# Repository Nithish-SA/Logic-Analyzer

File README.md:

# Logic-Analyzer
A 16 channel at 100Mhz Logic Analyzer which is supported by Cypress FX3 (USB 3.0 MCU).

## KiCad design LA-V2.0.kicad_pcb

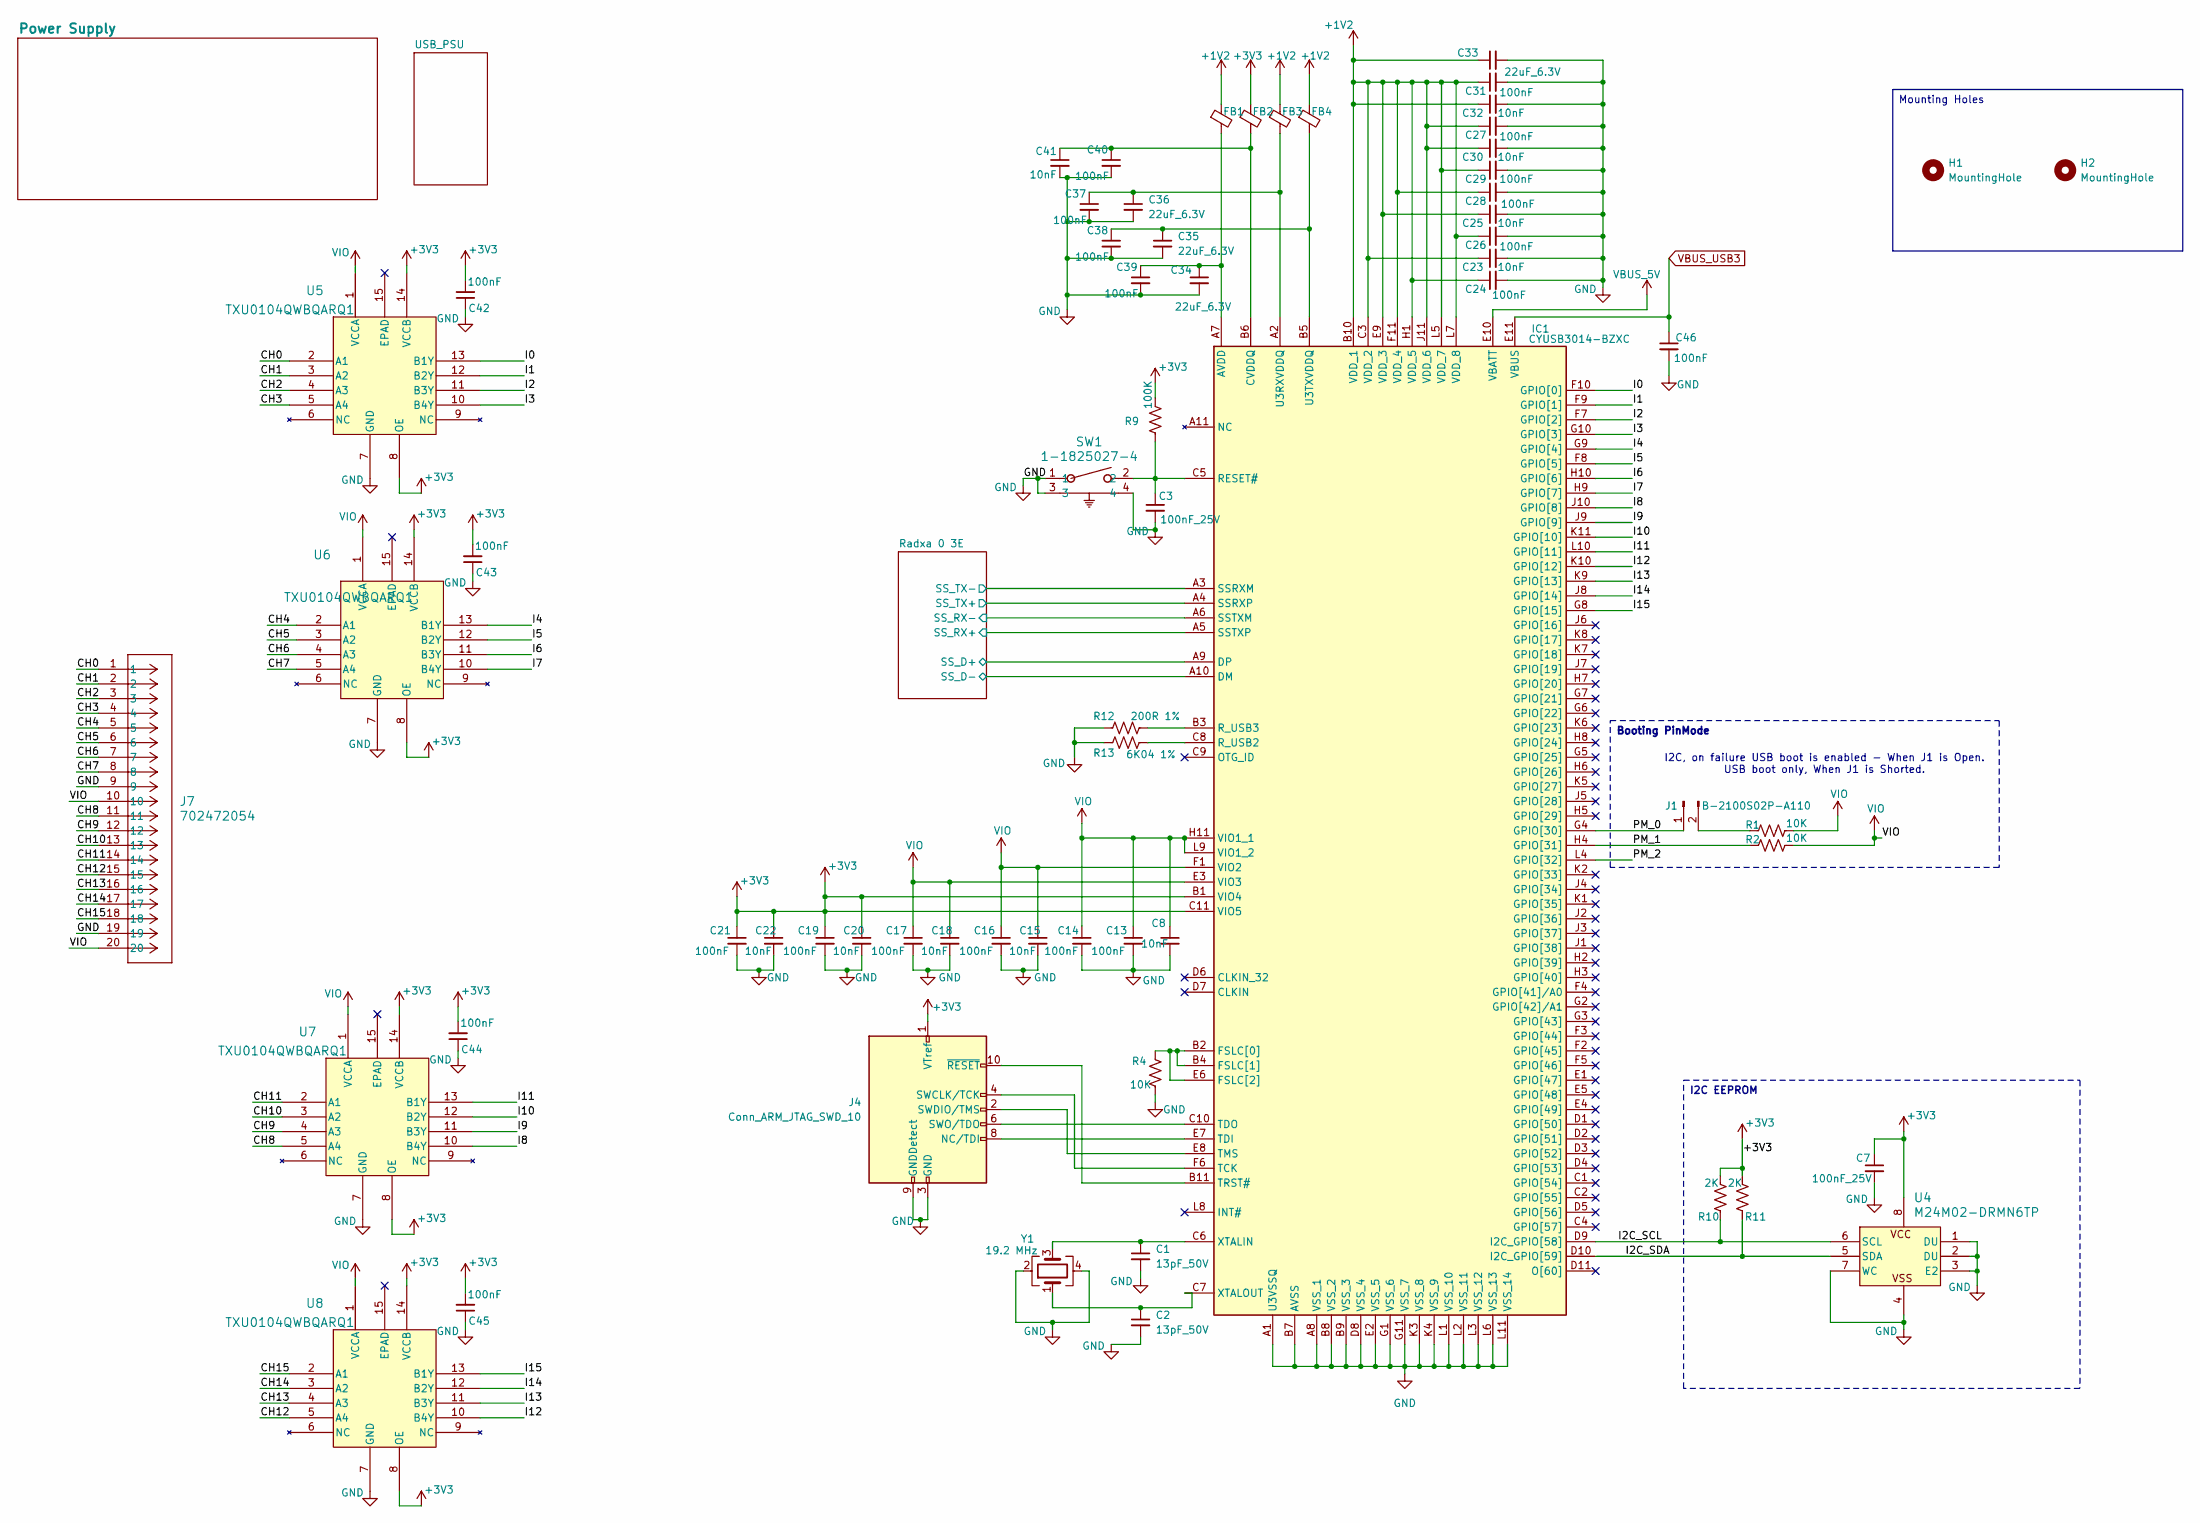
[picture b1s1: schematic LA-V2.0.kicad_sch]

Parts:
C1, C2: 13pF_50V; C_0402_1005Metric; LCSC Part# C161306
C3, C7: 100nF_25V; C_0402_1005Metric; LCSC Part# C155422
C8, C15, C18, C20, C22, C23, C25, C30, C32, C41: 10nF; C_0402_1005Metric; LCSC Part# C60133
C13, C14, C16, C17, C19, C21, C24, C26, C27, C28, C29, C31, C37, C38, C39, C40, C42, C43, C44, C45, C46: 100nF; C_0402_1005Metric; LCSC Part# C155422
C33: 22uF_6.3V; C_0805_2012Metric; LCSC Part# C5674
C34, C35, C36: 22uF_6.3V; C_0402_1005Metric; LCSC Part# C415703
FB1, FB2, FB3, FB4: FerriteBead_Small; L_0805_2012Metric; LCSC Part# C81034
H1, H2: MountingHole; MountingHole_2.7mm_M2.5_ISO14580_Pad_TopOnly
IC1: CYUSB3014-BZXC; Manufacturer_Part_Number CYUSB3014-BZXC; LCSC Part# C462526
J1: B-2100S02P-A110; PinHeader_1x02_P2.54mm_Vertical; LCSC Part# C124375
J4: Conn_ARM_JTAG_SWD_10; PinHeader_2x05_P2.54mm_Vertical; LCSC Part# C492422
J7: 702472054; CONN_7024720xx_MOL; LCSC Part# C17505050
R1, R2, R4: 10K; R_0402_1005Metric; LCSC Part# C60490
R9: 100K; R_0805_2012Metric; LCSC Part# C122537
R10, R11: 2K; R_0805_2012Metric; LCSC Part# C114572
R12: 200R 1%; R_0402_1005Metric; LCSC Part# C114764
R13: 6K04 1%; R_0805_2012Metric; LCSC Part# C3014413
SW1: 1-1825027-4; SW2_1825027-E_TEC; LCSC Part# C2928195
U4: M24M02-DRMN6TP; SO_RMN6TP_STM; LCSC Part# C115042
U5, U6, U7, U8: TXU0104QWBQARQ1; WQFN14_BQA_TEX; LCSC Part# C5217874
Y1: 19.2 MHz; Crystal_SMD_3225-4Pin_3.2x2.5mm; LCSC Part# C7294560

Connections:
+1V2: C23.1, C24.1, C25.1, C26.1, C27.1, C28.1, C29.1, C30.1, C31.1, C32.1, C33.1, FB1.1, FB3.1, FB4.1, IC1.B10 (VDD_1), IC1.C3 (VDD_2), IC1.E9 (VDD_3), IC1.F11 (VDD_4), IC1.H1 (VDD_5), IC1.J11 (VDD_6), IC1.L5 (VDD_7), IC1.L7 (VDD_8); also elsewhere on the board
+3V3: C7.1, C19.1, C20.1, C21.1, C22.1, C42.2, C43.2, C44.2, C45.2, FB2.1, IC1.B1 (VIO4), IC1.C11 (VIO5), J4.1 (VTref), R9.2, R10.2, R11.2, U4.8, U5.8 (OE), U5.14 (VCCB), U6.8 (OE), U6.14 (VCCB), U7.8 (OE), U7.14 (VCCB), U8.8 (OE), U8.14 (VCCB); also elsewhere on the board
/CH0: J7.1, U5.2 (A1)
/CH1: J7.2, U5.3 (A2)
/CH2: J7.3, U5.4 (A3)
/CH3: J7.4, U5.5 (A4)
/CH4: J7.5, U6.2 (A1)
/CH5: J7.6, U6.3 (A2)
/CH6: J7.7, U6.4 (A3)
/CH7: J7.8, U6.5 (A4)
/CH8: J7.11, U7.5 (A4)
/CH9: J7.12, U7.4 (A3)
/CH10: J7.13, U7.3 (A2)
/CH11: J7.14, U7.2 (A1)
/CH12: J7.15, U8.5 (A4)
/CH13: J7.16, U8.4 (A3)
/CH14: J7.17, U8.3 (A2)
/CH15: J7.18, U8.2 (A1)
/I0: IC1.F10 (GPIO[0]), U5.13 (B1Y)
/I1: IC1.F9 (GPIO[1]), U5.12 (B2Y)
/I2: IC1.F7 (GPIO[2]), U5.11 (B3Y)
/I2C_SCL: IC1.D9 (I2C_GPIO[58]), R10.1, U4.6 (SCL)
/I2C_SDA: IC1.D10 (I2C_GPIO[59]), R11.1, U4.5 (SDA)
/I3: IC1.G10 (GPIO[3]), U5.10 (B4Y)
/I4: IC1.G9 (GPIO[4]), U6.13 (B1Y)
/I5: IC1.F8 (GPIO[5]), U6.12 (B2Y)
/I6: IC1.H10 (GPIO[6]), U6.11 (B3Y)
/I7: IC1.H9 (GPIO[7]), U6.10 (B4Y)
/I8: IC1.J10 (GPIO[8]), U7.10 (B4Y)
/I9: IC1.J9 (GPIO[9]), U7.11 (B3Y)
/I10: IC1.K11 (GPIO[10]), U7.12 (B2Y)
/I11: IC1.L10 (GPIO[11]), U7.13 (B1Y)
/I12: IC1.K10 (GPIO[12]), U8.10 (B4Y)
/I13: IC1.K9 (GPIO[13]), U8.11 (B3Y)
/I14: IC1.J8 (GPIO[14]), U8.12 (B2Y)
/I15: IC1.G8 (GPIO[15]), U8.13 (B1Y)
/PM_0: IC1.G4 (GPIO[30]), J1.1
/PM_1: IC1.H4 (GPIO[31]), R2.1
/PM_2: IC1.L4 (GPIO[32])
/Radxa 0 3E/SS_D+: IC1.A9 (DP); also elsewhere on the board
/Radxa 0 3E/SS_D-: IC1.A10 (DM); also elsewhere on the board
/Radxa 0 3E/SS_RX+: IC1.A5 (SSTXP); also elsewhere on the board
/Radxa 0 3E/SS_RX-: IC1.A6 (SSTXM); also elsewhere on the board
/Radxa 0 3E/SS_TX+: IC1.A4 (SSRXP); also elsewhere on the board
/Radxa 0 3E/SS_TX-: IC1.A3 (SSRXM); also elsewhere on the board
GND: C1.2, C2.2, C3.2, C7.2, C8.2, C13.2, C14.2, C15.2, C16.2, C17.2, C18.2, C19.2, C20.2, C21.2, C22.2, C23.2, C24.2, C25.2, C26.2, C27.2, C28.2, C29.2, C30.2, C31.2, C32.2, C33.2, C34.2, C35.2, C36.2, C37.2, C38.2, C39.2, C40.2, C41.2, C42.1, C43.1, C44.1, C45.1, C46.2, IC1.A1 (U3VSSQ), IC1.A8 (VSS_1), IC1.B7 (AVSS), IC1.B8 (VSS_2), IC1.B9 (VSS_3), IC1.D8 (VSS_4), IC1.E2 (VSS_5), IC1.G1 (VSS_6), IC1.G11 (VSS_7), IC1.K3 (VSS_8), IC1.K4 (VSS_9), IC1.L1 (VSS_10), IC1.L2 (VSS_11), IC1.L3 (VSS_12), IC1.L6 (VSS_13), IC1.L11 (VSS_14), J4.3 (GND), J4.5 (GND), J4.9 (GNDDetect), J7.9, J7.19, R4.1, R12.2, R13.2, SW1.1, SW1.3, SW1.4, U4.1 (DU), U4.2 (DU), U4.3 (E2), U4.4, U4.7 (WC), U5.7 (GND), U6.7 (GND), U7.7 (GND), U8.7 (GND), Y1.2, Y1.4; also elsewhere on the board
unnamed: C34.1, C39.1, FB1.2, IC1.A7 (AVDD)
unnamed: C40.1, C41.1, FB2.2, IC1.B6 (CVDDQ)
unnamed: IC1.B2 (FSLC[0]), IC1.B4 (FSLC[1]), IC1.E6 (FSLC[2]), R4.2
unnamed: C3.1, IC1.C5 (RESET#), R9.1, SW1.2
unnamed: IC1.C8 (R_USB2), R13.1
unnamed: IC1.B3 (R_USB3), R12.1
unnamed: IC1.F6 (TCK), J4.4 (SWCLK/TCK)
unnamed: IC1.E7 (TDI), J4.8 (NC/TDI)
unnamed: IC1.C10 (TDO), J4.6 (SWO/TDO)
unnamed: IC1.E8 (TMS), J4.2 (SWDIO/TMS)
unnamed: IC1.B11 (TRST#), J4.10 (~RESET)
unnamed: C36.1, C37.1, FB3.2, IC1.A2 (U3RXVDDQ)
unnamed: C35.1, C38.1, FB4.2, IC1.B5 (U3TXVDDQ)
unnamed: C1.1, IC1.C6 (XTALIN), Y1.3
unnamed: C2.1, IC1.C7 (XTALOUT), Y1.1
unnamed: J1.2, R1.1
VBUS_5V: IC1.E10 (VBATT); also elsewhere on the board
VBUS_USB3: C46.1, IC1.E11 (VBUS); also elsewhere on the board
VIO: C8.1, C13.1, C14.1, C15.1, C16.1, C17.1, C18.1, IC1.E3 (VIO3), IC1.F1 (VIO2), IC1.H11 (VIO1_1), IC1.L9 (VIO1_2), J7.10, J7.20, R1.2, R2.2, U5.1 (VCCA), U6.1 (VCCA), U7.1 (VCCA), U8.1 (VCCA); also elsewhere on the board

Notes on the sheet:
I2C, on failure USB boot is enabled - When J1 is Open. USB boot only, When J1 is Shorted.
Booting PinMode
I2C EEPROM
Mounting Holes

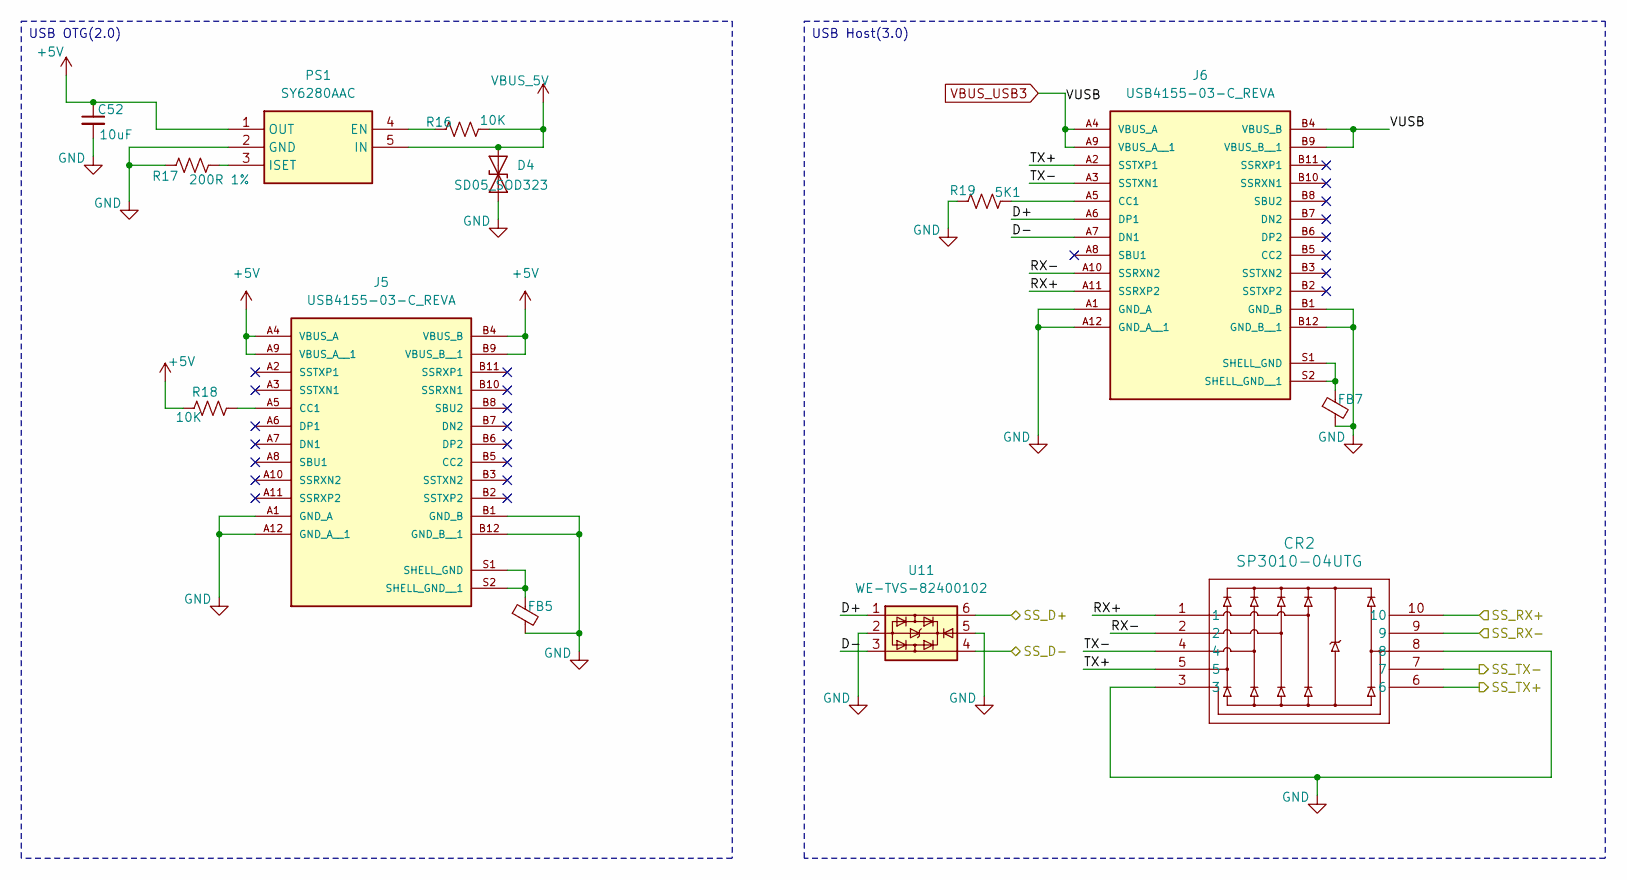
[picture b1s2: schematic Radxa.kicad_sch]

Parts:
C52: 10uF; C_0402_1005Metric; LCSC Part# C32635
CR2: SP3010-04UTG; UDFEN-10_MO229_LTF-L; LCSC Part# C126837
D4: SD05_SOD323; D_SOD-323
FB5, FB7: FerriteBead_Small; L_0805_2012Metric; LCSC Part# C81034
J5, J6: USB4155-03-C_REVA; USB Plug-GCT_USB4155-03-C_REVA; PARTREV A
PS1: SY6280AAC; SOT95P285X140-5N; Manufacturer_Part_Number SY6280AAC
R16, R18: 10K; R_0402_1005Metric; LCSC Part# C60490
R17: 200R 1%; R_0402_1005Metric; LCSC Part# C114764
R19: 5K1; R_0402_1005Metric; LCSC Part# C351692
U11: WE-TVS-82400102; SOT-23-6; LCSC Part# C22435120

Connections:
+5V: C52.1, J5.A4 (VBUS_A), J5.A9 (VBUS_A__1), J5.B4 (VBUS_B), J5.B9 (VBUS_B__1), PS1.1 (OUT), R18.1
/Radxa 0 3E/D+: J6.A6 (DP1), U11.1
/Radxa 0 3E/D-: J6.A7 (DN1), U11.3
/Radxa 0 3E/RX+: CR2.1, J6.A11 (SSRXP2)
/Radxa 0 3E/RX-: CR2.2, J6.A10 (SSRXN2)
/Radxa 0 3E/SS_D+: U11.6; also elsewhere on the board
/Radxa 0 3E/SS_D-: U11.4; also elsewhere on the board
/Radxa 0 3E/SS_RX+: CR2.10; also elsewhere on the board
/Radxa 0 3E/SS_RX-: CR2.9; also elsewhere on the board
/Radxa 0 3E/SS_TX+: CR2.6; also elsewhere on the board
/Radxa 0 3E/SS_TX-: CR2.7; also elsewhere on the board
/Radxa 0 3E/TX+: CR2.5, J6.A2 (SSTXP1)
/Radxa 0 3E/TX-: CR2.4, J6.A3 (SSTXN1)
GND: C52.2, CR2.3, CR2.8, D4.1 (A1), FB5.2, FB7.2, J5.A1 (GND_A), J5.A12 (GND_A__1), J5.B1 (GND_B), J5.B12 (GND_B__1), J6.A1 (GND_A), J6.A12 (GND_A__1), J6.B1 (GND_B), J6.B12 (GND_B__1), PS1.2 (GND), R17.2, R19.2, U11.2, U11.5; also elsewhere on the board
unnamed: J5.A5 (CC1), R18.2
unnamed: FB5.1, J5.S1 (SHELL_GND), J5.S2 (SHELL_GND__1)
unnamed: J6.A5 (CC1), R19.1
unnamed: FB7.1, J6.S1 (SHELL_GND), J6.S2 (SHELL_GND__1)
unnamed: PS1.4 (EN), R16.1
unnamed: PS1.3 (ISET), R17.1
VBUS_5V: D4.2 (A2), PS1.5 (IN), R16.2; also elsewhere on the board
VBUS_USB3: J6.A4 (VBUS_A), J6.A9 (VBUS_A__1), J6.B4 (VBUS_B), J6.B9 (VBUS_B__1); also elsewhere on the board

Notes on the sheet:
USB OTG(2.0)
USB Host(3.0)

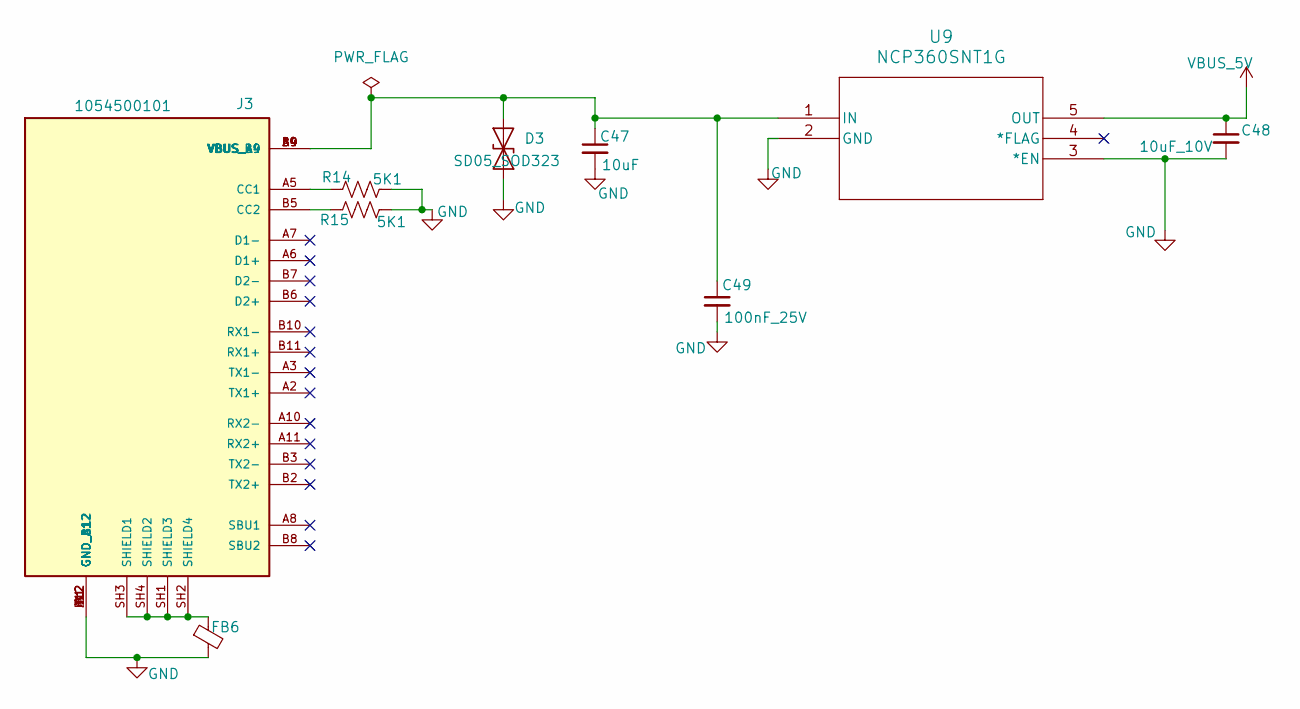
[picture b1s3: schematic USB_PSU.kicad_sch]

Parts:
C47: 10uF; C_0402_1005Metric; LCSC Part# C32635
C48: 10uF_10V; C_0402_1005Metric; LCSC Part# C32635
C49: 100nF_25V; C_0402_1005Metric; LCSC Part# C155422
D3: SD05_SOD323; D_SOD-323
FB6: FerriteBead_Small; L_0805_2012Metric; LCSC Part# C81034
J3: 1054500101; MOLEX_1054500101; PARTREV A7; LCSC Part# C134092
R14, R15: 5K1; R_0402_1005Metric; LCSC Part# C351692
U9: NCP360SNT1G; TSOP5_3X1P5_ONS; LCSC Part# C603707

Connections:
GND: C47.2, C48.2, C49.2, D3.1 (A1), FB6.2, J3.A1 (GND_A1), J3.A12 (GND_A12), J3.B1 (GND_B1), J3.B12 (GND_B12), R14.1, R15.1, U9.2 (GND), U9.3 (*EN); also elsewhere on the board
unnamed: C47.1, C49.1, D3.2 (A2), J3.A4 (VBUS_A4), J3.A9 (VBUS_A9), J3.B4 (VBUS_B4), J3.B9 (VBUS_B9), U9.1 (IN)
unnamed: J3.A5 (CC1), R14.2
unnamed: J3.B5 (CC2), R15.2
unnamed: FB6.1, J3.SH1 (SHIELD3), J3.SH2 (SHIELD4), J3.SH3 (SHIELD1), J3.SH4 (SHIELD2)
VBUS_5V: C48.1, U9.5 (OUT); also elsewhere on the board

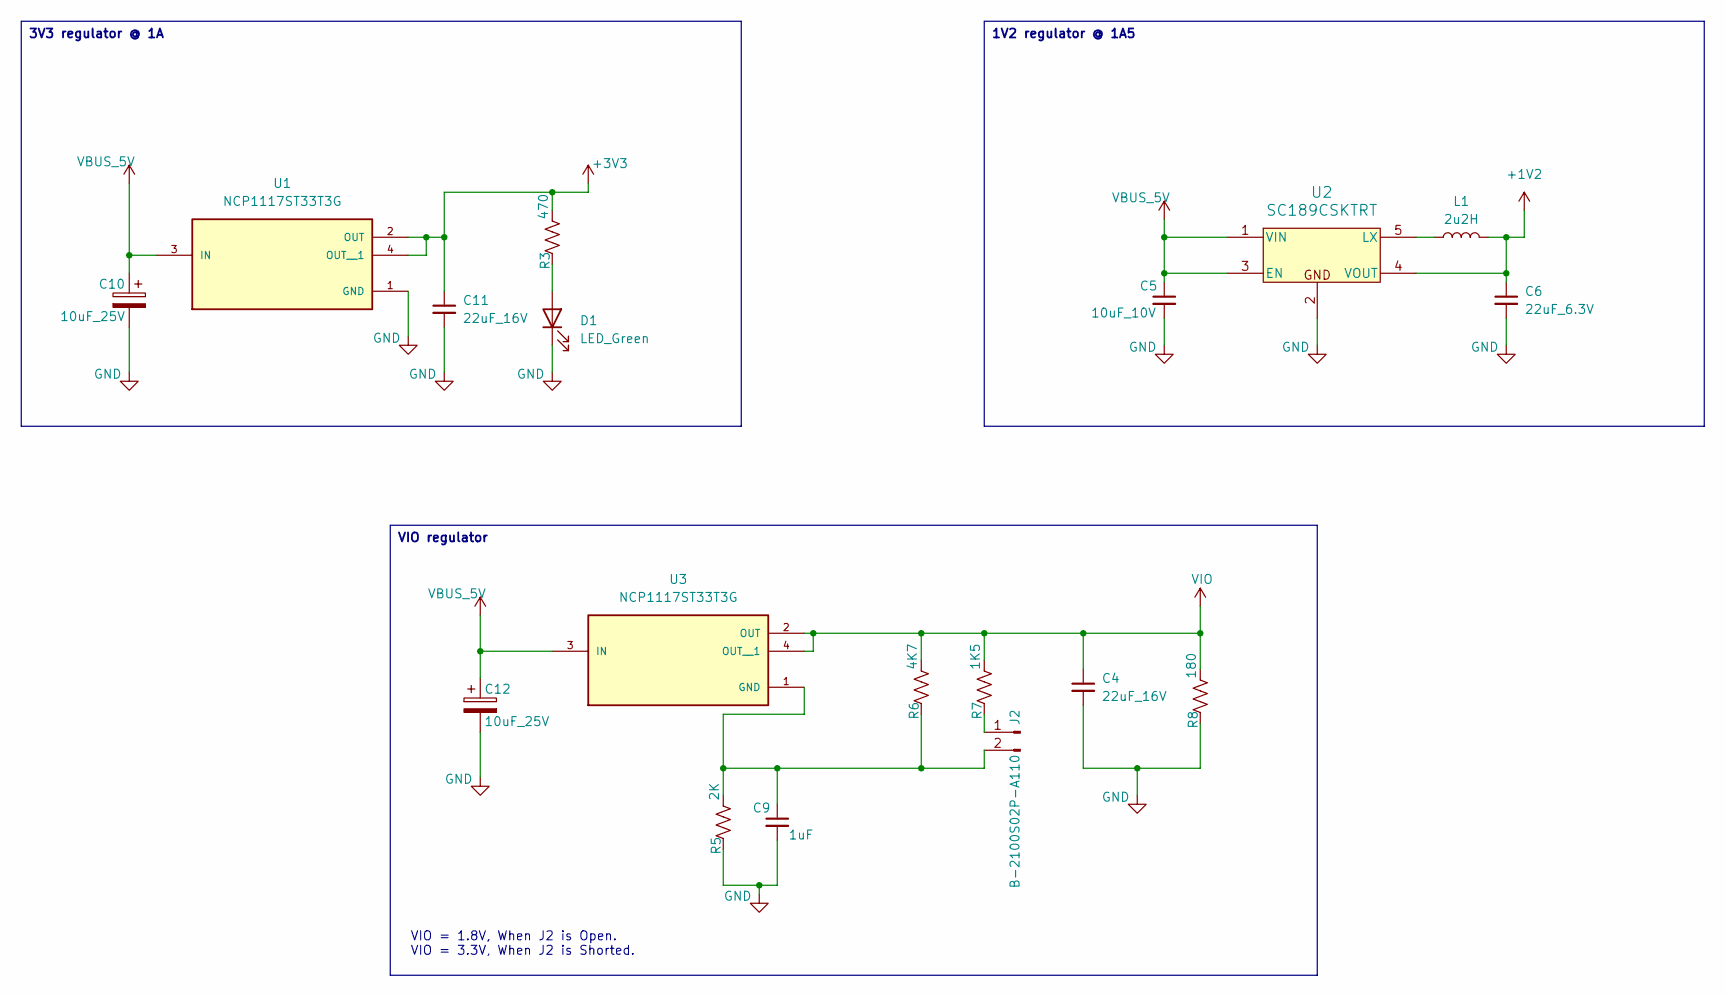
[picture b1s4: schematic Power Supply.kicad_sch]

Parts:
C4, C11: 22uF_16V; C_0805_2012Metric; LCSC Part# C296720
C5: 10uF_10V; C_0805_2012Metric; LCSC Part# C32635
C6: 22uF_6.3V; C_0805_2012Metric; LCSC Part# C5674
C9: 1uF; C_0603_1608Metric; Mfg PN CL10A105KP8NNNC; LCSC Part# C26413
C10, C12: 10uF_25V; CP_EIA-3528-12_Kemet-T; LCSC Part# C382102
D1: LED_Green; LED_0805_2012Metric; LCSC Part# C98221
J2: B-2100S02P-A110; PinHeader_1x02_P2.54mm_Vertical; LCSC Part# C124375
L1: 2u2H; L_0805_2012Metric; LCSC Part# C711165
R3: 470; R_0603_1608Metric; LCSC Part# C881392
R5: 2K; R_0805_2012Metric; LCSC Part# C114572
R6: 4K7; R_0805_2012Metric; LCSC Part# C60816
R7: 1K5; R_0805_2012Metric; LCSC Part# C865270
R8: 180; R_0805_2012Metric; LCSC Part# C137585
U1, U3: NCP1117ST33T3G; SOT230P700X180-4N
U2: SC189CSKTRT; SOT_CSKTRT_SEM; LCSC Part# C783594

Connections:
+1V2: C6.1, L1.2, U2.4 (VOUT); also elsewhere on the board
+3V3: C11.1, R3.2, U1.2 (OUT), U1.4 (OUT__1); also elsewhere on the board
GND: C4.2, C5.2, C6.2, C9.2, C10.2, C11.2, C12.2, D1.1 (K), R5.1, R8.1, U1.1 (GND), U2.2; also elsewhere on the board
unnamed: D1.2 (A), R3.1
unnamed: J2.1, R7.1
unnamed: C9.1, J2.2, R5.2, R6.1, U3.1 (GND)
unnamed: L1.1, U2.5 (LX)
VBUS_5V: C5.1, C10.1, C12.1, U1.3 (IN), U2.1 (VIN), U2.3 (EN), U3.3 (IN); also elsewhere on the board
VIO: C4.1, R6.2, R7.2, R8.2, U3.2 (OUT), U3.4 (OUT__1); also elsewhere on the board

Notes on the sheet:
VIO = 1.8V, When J2 is Open. VIO = 3.3V, When J2 is Shorted.
3V3 regulator @ 1A
VIO regulator
1V2 regulator @ 1A5

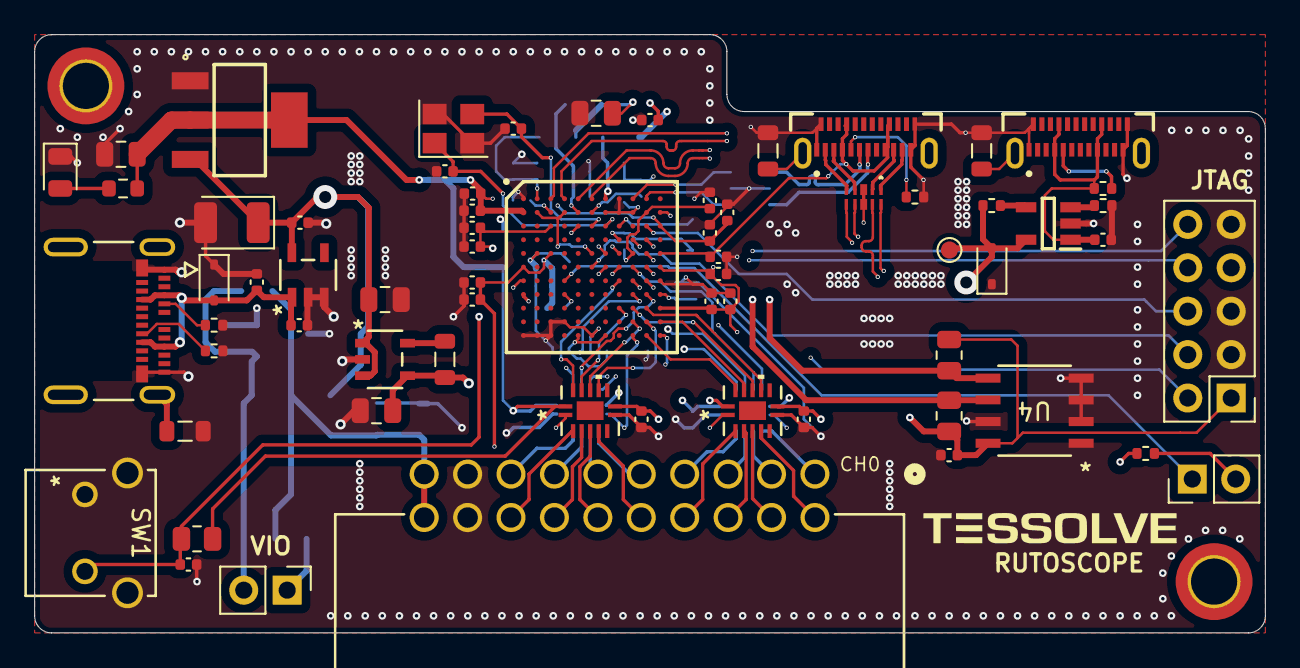
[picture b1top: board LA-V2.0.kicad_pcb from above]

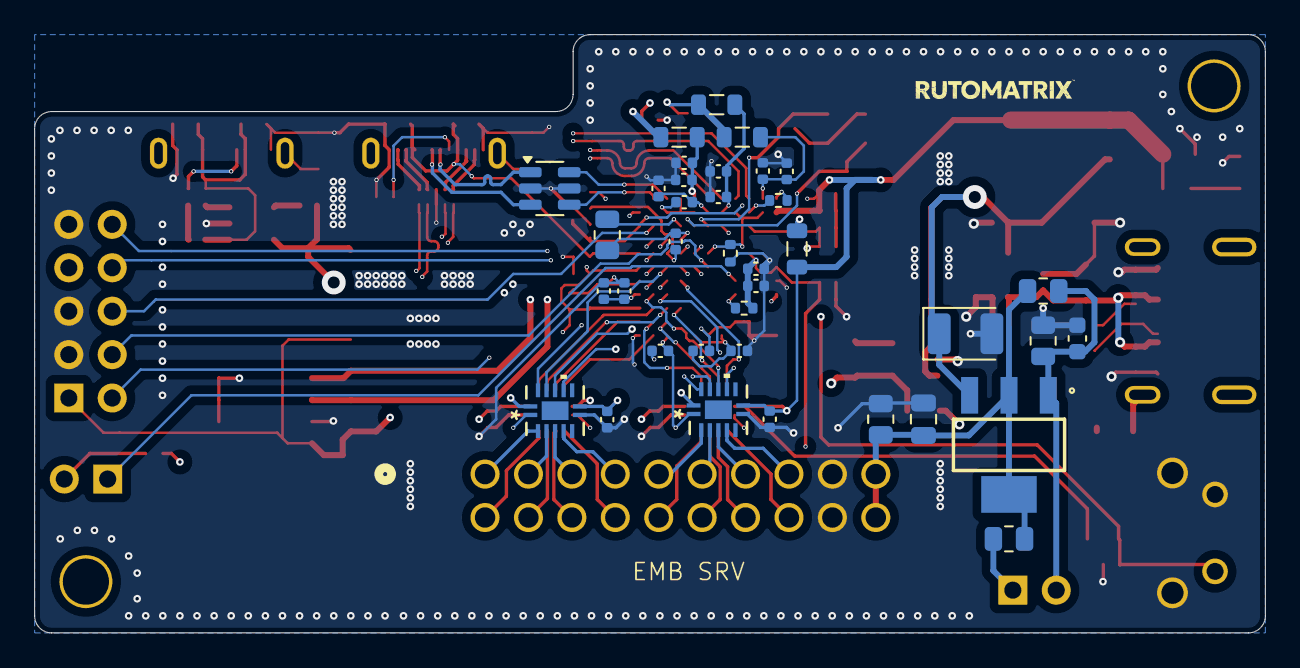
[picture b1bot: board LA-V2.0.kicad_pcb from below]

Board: 4 copper layers, 72.0 x 35.0 mm, 105 parts (37 on the bottom side), 85 nets.

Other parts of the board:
TP1: TestPoint_Pad_D1.0mm

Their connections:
VBUS_5V: TP1.1; also elsewhere on the board

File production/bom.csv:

Designator,Footprint,Quantity,Value,LCSC Part #
"C1, C2",0402,2,13pF_50V,
"C10, C12",CP_EIA-3528-12_Kemet-T,2,10uF_25V,
"C11, C4",0805,2,22uF_16V,
"C13, C14, C16, C17, C19, C21, C24, C26, C27, C28, C29, C31, C37, C38, C39, C40, C42, C43, C44, C45, C46",0402,21,100nF,
"C15, C18, C20, C22, C23, C25, C30, C32, C41, C8",0402,10,10nF,
"C3, C49, C7",0402,3,100nF_25V,
"C33, C6",0805,2,22uF_6.3V,
"C34, C35, C36",0402,3,22uF_6.3V,
"C47, C52",0402,2,10uF,
C48,0402,1,10uF_10V,
C5,0805,1,10uF_10V,
C9,0603,1,1uF,
CR2,UDFEN-10_MO229_LTF-L,1,SP3010-04UTG,
D1,0805,1,LED_Green,
"D3, D4",D_SOD-323,2,SD05_SOD323,
"FB1, FB2, FB3, FB4, FB5, FB6, FB7",0805,7,FerriteBead_Small,
IC1,CYUSB3014-BZXC,1,CYUSB3014-BZXC,
"J1, J2",PinHeader_1x02_P2.54mm_Vertical,2,B-2100S02P-A110,
J3,MOLEX_1054500101,1,1054500101,
J4,PinHeader_2x05_P2.54mm_Vertical,1,Conn_ARM_JTAG_SWD_10,
"J5, J6",USB Plug-GCT_USB4155-03-C_REVA,2,USB4155-03-C_REVA,
J7,CONN_7024720xx_MOL,1,702472054,
L1,0805,1,2u2H,
PS1,SOT95P285X140-5N,1,SY6280AAC,
"R1, R16, R18, R2, R4",0402,5,10K,
"R10, R11, R5",0805,3,2K,
"R12, R17",0402,2,200R 1%,
R13,0805,1,6K04 1%,
"R14, R15, R19",0402,3,5K1,
R3,0603,1,470,
R6,0805,1,4K7,
R7,0805,1,1K5,
R8,0805,1,180,
R9,0805,1,100K,
SW1,SW2_1825027-E_TEC,1,1-1825027-4,
"U1, U3",SOT230P700X180-4N,2,NCP1117ST33T3G,
U11,SOT-23-6,1,WE-TVS-82400102,
U2,SOT_CSKTRT_SEM,1,SC189CSKTRT,
U4,SO_RMN6TP_STM,1,M24M02-DRMN6TP,
"U5, U6, U7, U8",WQFN14_BQA_TEX,4,TXU0104QWBQARQ1,
U9,TSOP5_3X1P5_ONS,1,NCP360SNT1G,
Y1,Crystal_SMD_3225-4Pin_3.2x2.5mm,1,19.2 MHz,
